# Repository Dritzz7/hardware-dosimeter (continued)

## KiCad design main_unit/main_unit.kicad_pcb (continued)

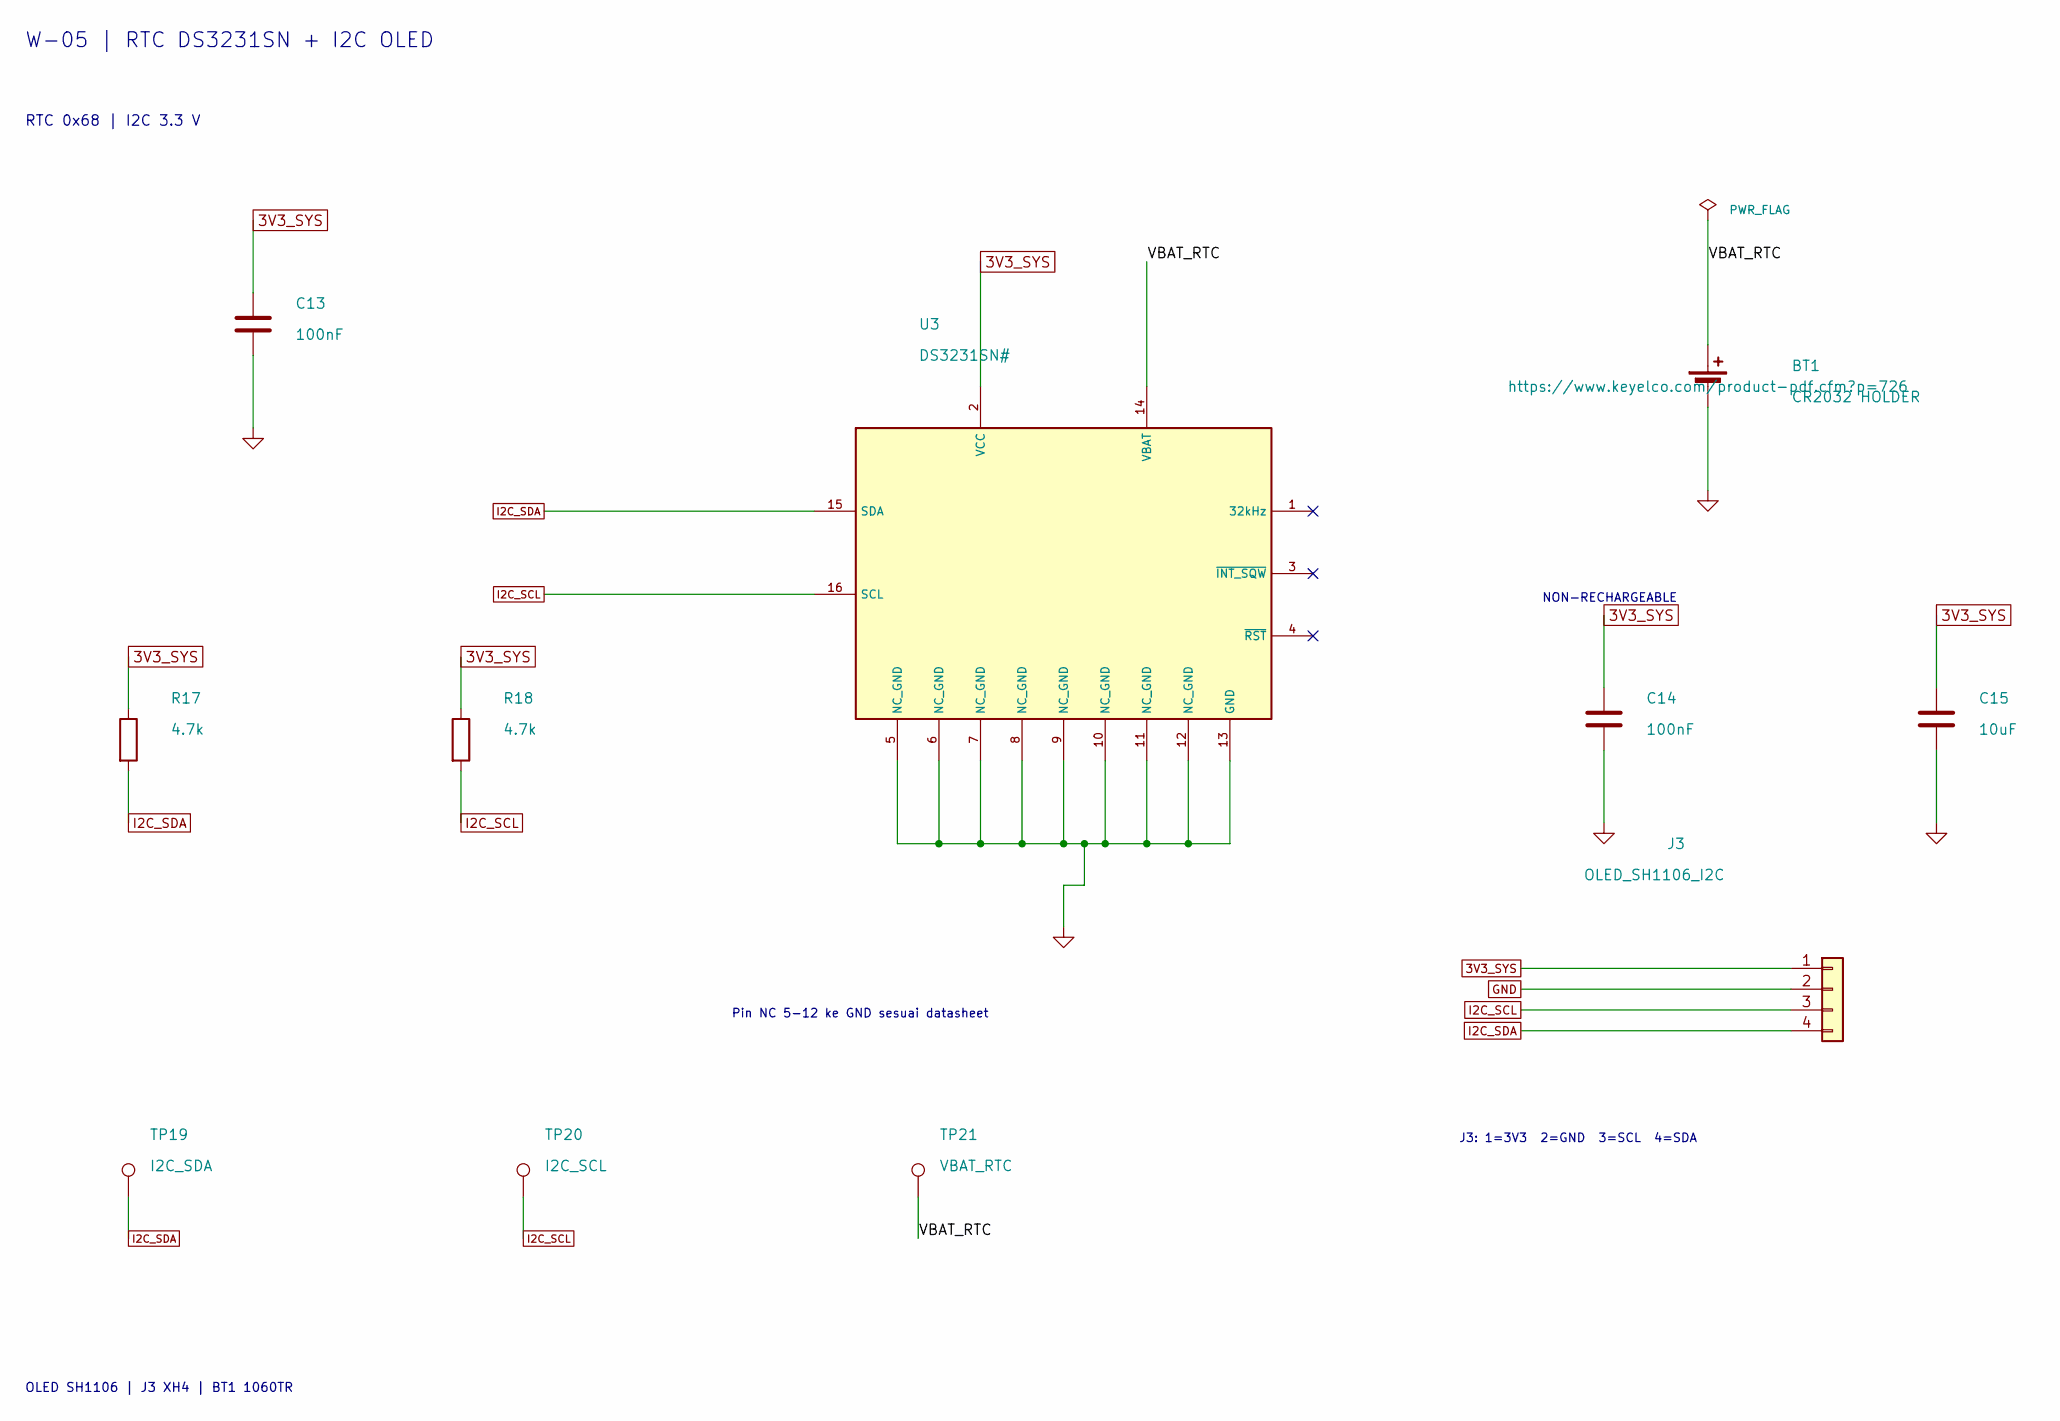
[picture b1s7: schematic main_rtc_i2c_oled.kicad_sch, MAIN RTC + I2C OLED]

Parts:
BT1: CR2032 HOLDER; BatteryHolder_Keystone_1060TR_1x2032; MPN 1060TR; LCSC Part # C238069
C13, C14: 100nF; C_0805_2012Metric; MPN C0805C104K5RACTU; LCSC Part # C3018562
C15: 10uF; C_0805_2012Metric; MPN CL21A106KAYNNNE; LCSC Part # C15850
J3: OLED_SH1106_I2C; JST_XH_B4B-XH-A_1x04_P2.50mm_Vertical; MPN B4B-XH-A(LF)(SN); LCSC Part # C144395
R17, R18: 4.7k; R_0805_2012Metric; MPN RC0805FR-074K7L; LCSC Part # C60816
TP19: I2C_SDA; TestPoint_Pad_D1.5mm; MPN N/A - PCB copper feature
TP20: I2C_SCL; TestPoint_Pad_D1.5mm; MPN N/A - PCB copper feature
TP21: VBAT_RTC; TestPoint_Pad_D1.5mm; MPN N/A - PCB copper feature
U3: DS3231SN#; SOIC-16W_7.5x10.3mm_P1.27mm; MPN DS3231SN#; LCSC Part # C5369307

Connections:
3V3_SYS: C13.1, C14.1, C15.1, J3.1, R17.1, R18.1, U3.2 (VCC); also elsewhere on the board
/MAIN_RTC_I2C_OLED/VBAT_RTC: BT1.1 (+), TP21.1 (1_1), U3.14 (VBAT)
GND: BT1.2 (-), C13.2, C14.2, C15.2, J3.2, U3.5 (NC_GND), U3.6 (NC_GND), U3.7 (NC_GND), U3.8 (NC_GND), U3.9 (NC_GND), U3.10 (NC_GND), U3.11 (NC_GND), U3.12 (NC_GND), U3.13 (GND); also elsewhere on the board
I2C_SCL: J3.3, R18.2, TP20.1 (1_1), U3.16 (SCL); also elsewhere on the board
I2C_SDA: J3.4, R17.2, TP19.1 (1_1), U3.15 (SDA); also elsewhere on the board

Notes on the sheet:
W-05 | RTC DS3231SN + I2C OLED
NON-RECHARGEABLE
J3: 1=3V3 2=GND 3=SCL 4=SDA
Pin NC 5-12 ke GND sesuai datasheet
OLED SH1106 | J3 XH4 | BT1 1060TR
RTC 0x68 | I2C 3.3 V

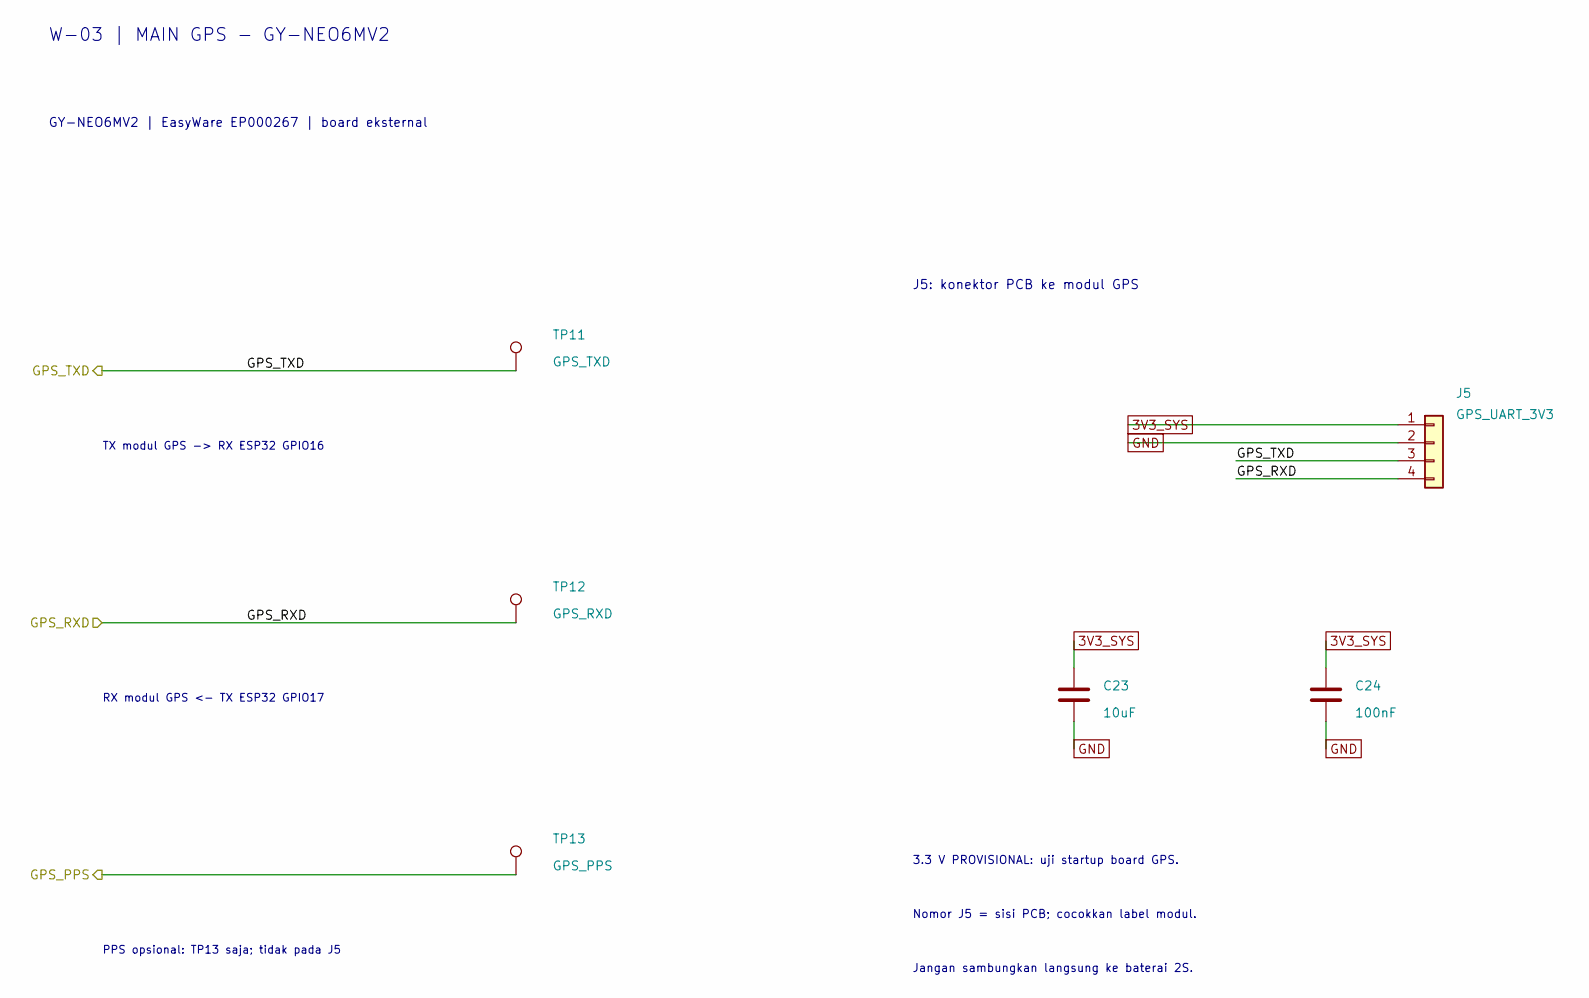
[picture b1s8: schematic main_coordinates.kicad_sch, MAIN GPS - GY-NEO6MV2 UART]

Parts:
C23: 10uF; C_0805_2012Metric; Voltage_Rating >=6.3V; MPN CL21A106KAYNNNE; LCSC Part # C15850
C24: 100nF; C_0805_2012Metric; Voltage_Rating >=6.3V; MPN C0805C104K5RACTU; LCSC Part # C3018562
J5: GPS_UART_3V3; JST_XH_B4B-XH-A_1x04_P2.50mm_Vertical; MPN B4B-XH-A(LF)(SN); LCSC Part # C144395
TP11: GPS_TXD; TestPoint_Pad_D1.5mm; MPN N/A - PCB copper feature
TP12: GPS_RXD; TestPoint_Pad_D1.5mm; MPN N/A - PCB copper feature
TP13: GPS_PPS; TestPoint_Pad_D1.5mm; MPN N/A - PCB copper feature

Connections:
3V3_SYS: C23.1, C24.1, J5.1; also elsewhere on the board
/MAIN_ESP32_PROGRAMMING/GPS_PPS: TP13.1 (1_1); also elsewhere on the board
/MAIN_ESP32_PROGRAMMING/GPS_RXD: J5.4, TP12.1 (1_1); also elsewhere on the board
/MAIN_ESP32_PROGRAMMING/GPS_TXD: J5.3, TP11.1 (1_1); also elsewhere on the board
GND: C23.2, C24.2, J5.2; also elsewhere on the board

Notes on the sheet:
GY-NEO6MV2 | EasyWare EP000267 | board eksternal
J5: konektor PCB ke modul GPS
RX modul GPS <- TX ESP32 GPIO17
PPS opsional: TP13 saja; tidak pada J5
W-03 | MAIN GPS - GY-NEO6MV2
TX modul GPS -> RX ESP32 GPIO16
3.3 V PROVISIONAL: uji startup board GPS.
Nomor J5 = sisi PCB; cocokkan label modul.
Jangan sambungkan langsung ke baterai 2S.

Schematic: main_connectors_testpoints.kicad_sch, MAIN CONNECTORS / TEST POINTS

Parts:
J1: PROG_UART_3V3; PinHeader_1x06_P2.54mm_ZHOURI_1.02mm; MPN 2.54-1*6; LCSC Part # C5156615
TP1: MAIN_EN; TestPoint_Pad_D1.5mm; MPN N/A - PCB copper feature
TP2: MAIN_GPIO0; TestPoint_Pad_D1.5mm; MPN N/A - PCB copper feature
TP3: UART_TX0; TestPoint_Pad_D1.5mm; MPN N/A - PCB copper feature
TP4: UART_RX0; TestPoint_Pad_D1.5mm; MPN N/A - PCB copper feature

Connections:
3V3_SYS: J1.2; also elsewhere on the board
GND: J1.1; also elsewhere on the board
MAIN_EN: J1.5, TP1.1 (1_1); also elsewhere on the board
MAIN_GPIO0: J1.6, TP2.1 (1_1); also elsewhere on the board
UART_RX0: J1.4, TP4.1 (1_1); also elsewhere on the board
UART_TX0: J1.3, TP3.1 (1_1); also elsewhere on the board

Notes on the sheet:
W-08 | MAIN CONNECTORS / TEST POINTS
1 GND | 2 3V3 reference
J4 / TP24-28: MAIN_POWER
RESET/BOOT di MCU | UART 3.3 V | J1 header 2.54 mm
SERVICE UART / PROGRAMMING
3 TX ESP -> RX adapter
TP5-10: MAIN_ADXL345
J1.2: reference only; jangan hubungkan output daya adapter
J1 - KONTRAK PIN PCB
J3 / TP19-21: MAIN_RTC_I2C_OLED
J2 / TP14-18: MAIN_MICROSD
4 RX ESP <- TX adapter
TP22-23: MAIN_HMI
J5 / TP11-13: MAIN_GPS
INDEKS - TETAP DI SHEET FUNGSINYA
5 EN | 6 GPIO0 / BOOT

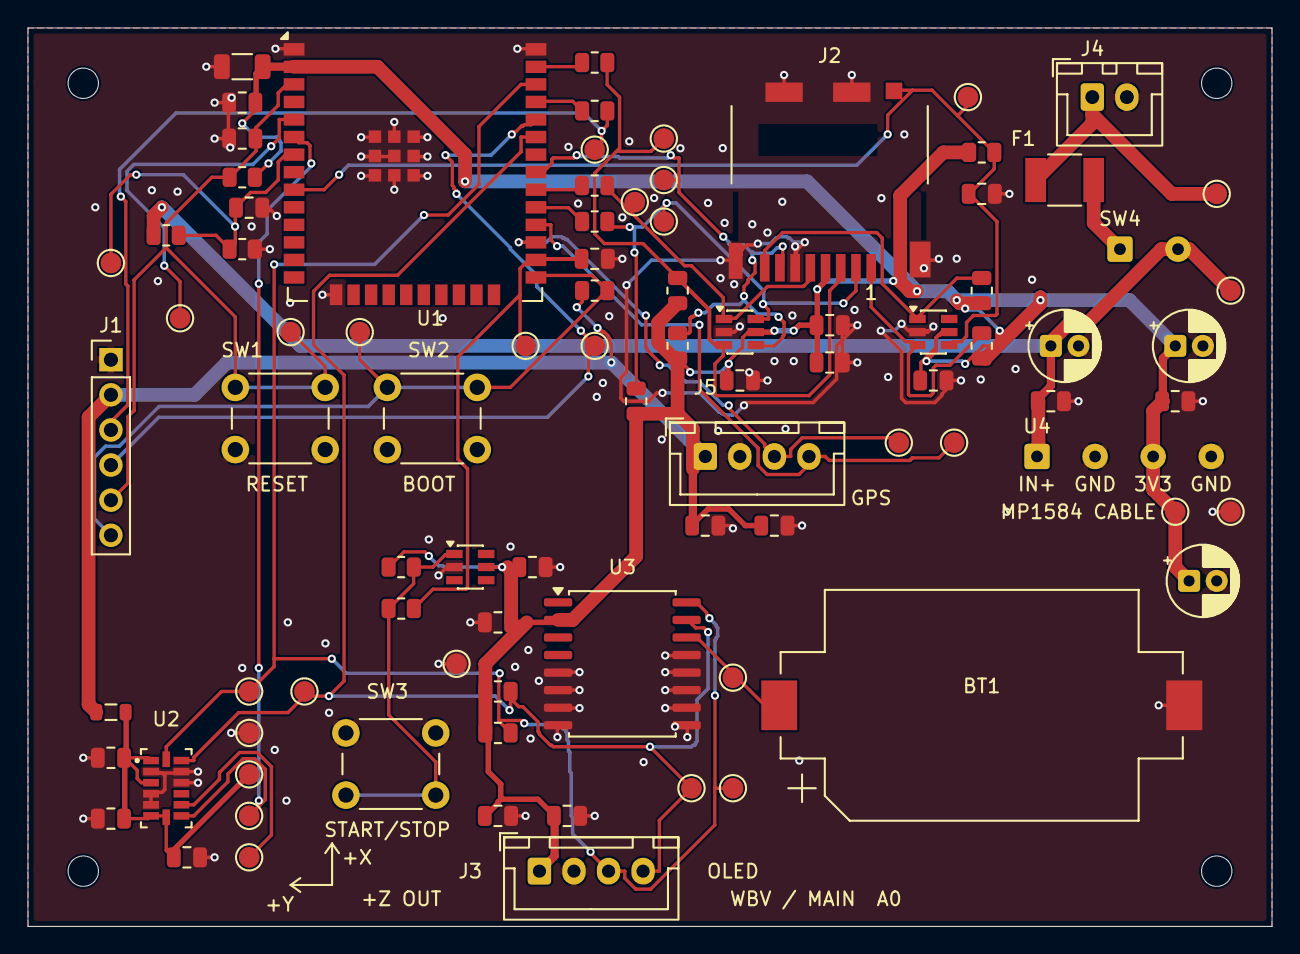
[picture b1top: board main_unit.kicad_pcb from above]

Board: 2 copper layers, 90.0 x 65.0 mm, 93 parts (0 on the bottom side), 32 nets.

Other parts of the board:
H1, H2, H3, H4: M2 mounting PROVISIONAL; MountingHole_2.2mm_M2

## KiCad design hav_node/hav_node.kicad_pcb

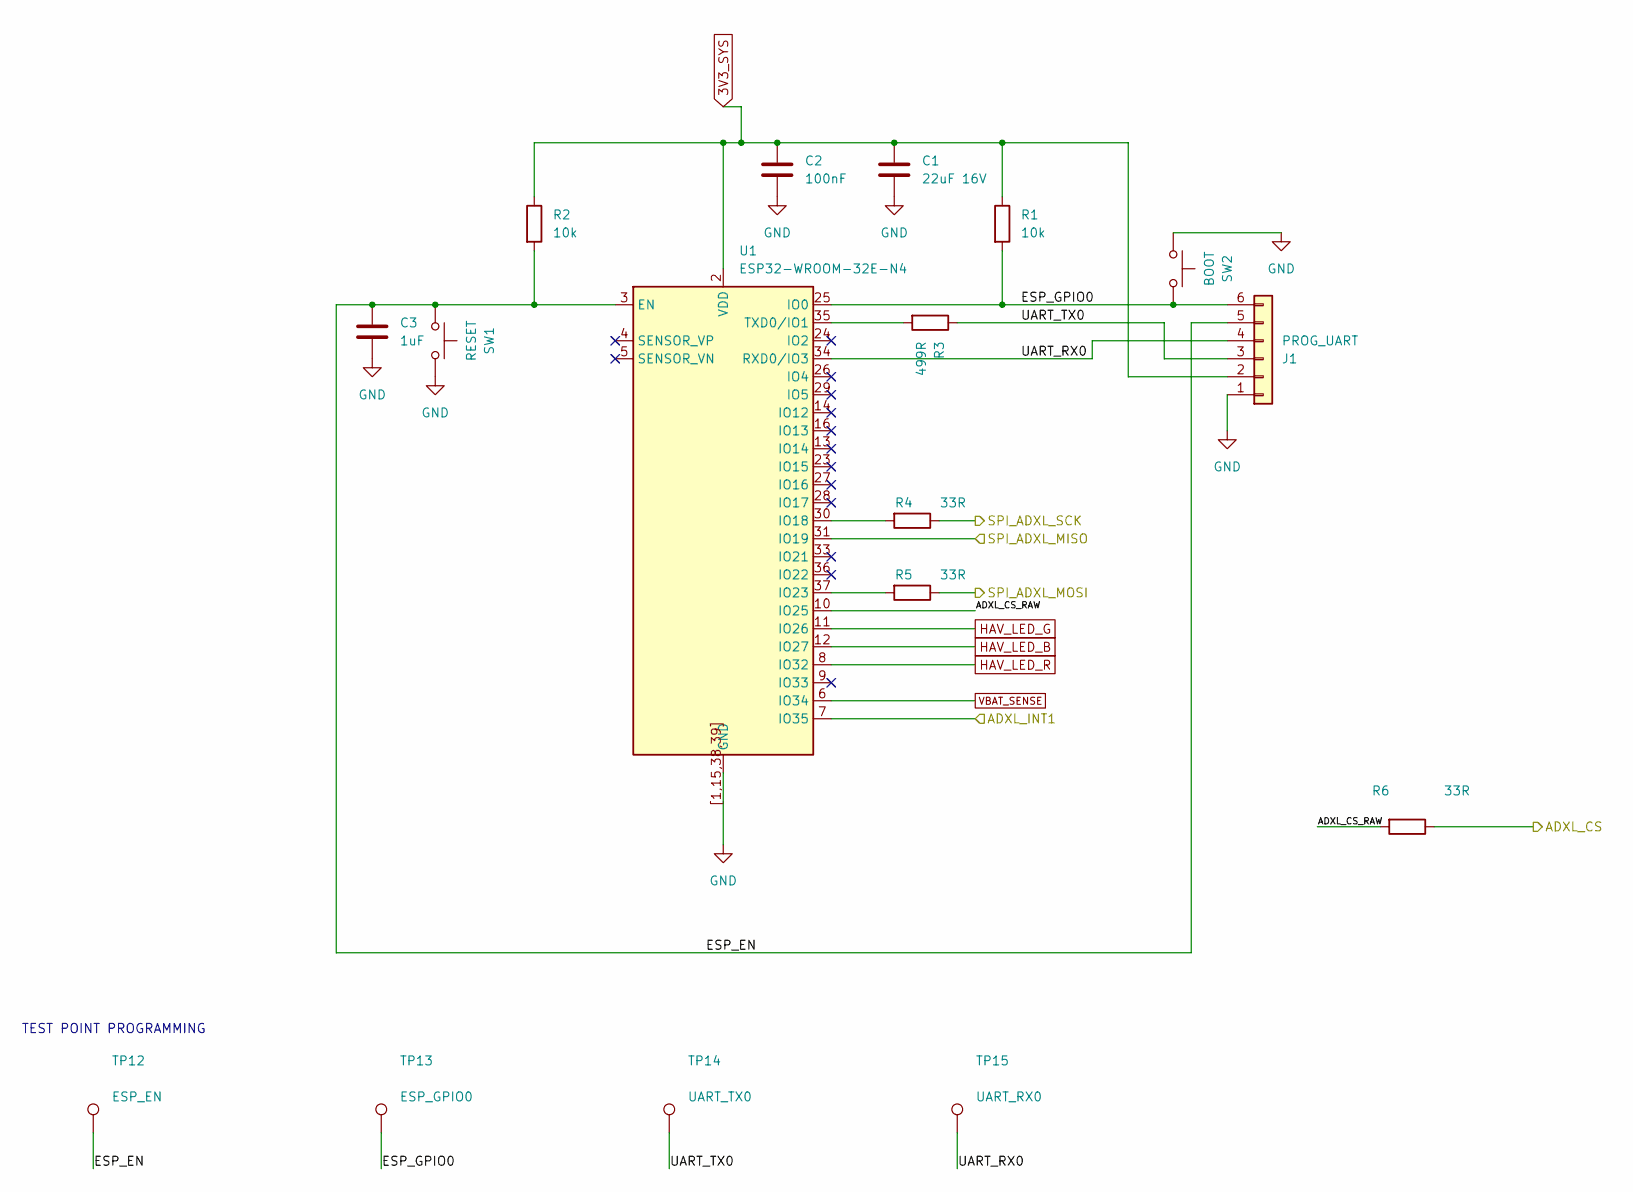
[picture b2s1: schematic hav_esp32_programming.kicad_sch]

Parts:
C1: 22uF 16V; C_1206_3216Metric; MPN CL31A226KOHNNNE; LCSC Part # C90146
C2: 100nF; C_0805_2012Metric; MPN C0805C104K5RACTU; LCSC Part # C3018562
C3: 1uF; C_0805_2012Metric; MPN C0805C105K4RACTU; LCSC Part # C2167376
J1: PROG_UART; PinHeader_1x06_P2.54mm_ZHOURI_1.02mm; MPN 2.54-1*6; LCSC Part # C5156615
R1, R2: 10k; R_0805_2012Metric; MPN RC0805FR-0710KL; LCSC Part # C84376
R3: 499R; R_0805_2012Metric; MPN RC0805FR-07499RL; LCSC Part # C130458
R4, R5, R6: 33R; R_0805_2012Metric; MPN RC0805FR-0733RL; LCSC Part # C126353
SW1: RESET; SW_PUSH_6mm_H4.3mm; MPN B3F-1000; LCSC Part # C93157
SW2: BOOT; SW_PUSH_6mm_H4.3mm; MPN B3F-1000; LCSC Part # C93157
TP12: ESP_EN; TestPoint_Pad_D1.5mm; MPN N/A - bare PCB pad
TP13: ESP_GPIO0; TestPoint_Pad_D1.5mm; MPN N/A - bare PCB pad
TP14: UART_TX0; TestPoint_Pad_D1.5mm; MPN N/A - bare PCB pad
TP15: UART_RX0; TestPoint_Pad_D1.5mm; MPN N/A - bare PCB pad
U1: ESP32-WROOM-32E-N4; ESP32-WROOM-32E_JLC_NoVia; MPN ESP32-WROOM-32E-N4; LCSC Part # C701341

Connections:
3V3_SYS: C1.1, C2.1, J1.2, R1.1, R2.1, U1.2 (VDD); also elsewhere on the board
/ADXL_CS: R6.1; also elsewhere on the board
/ADXL_INT1: U1.7 (IO35); also elsewhere on the board
/HAV_ESP32_PROGRAMMING/ADXL_CS_RAW: R6.2, U1.10 (IO25)
/HAV_ESP32_PROGRAMMING/ESP_EN: C3.1, J1.5, R2.2, SW1.1, TP12.1 (1_1), U1.3 (EN)
/HAV_ESP32_PROGRAMMING/ESP_GPIO0: J1.6, R1.2, SW2.2, TP13.1 (1_1), U1.25 (IO0)
/HAV_ESP32_PROGRAMMING/UART_RX0: J1.4, TP15.1 (1_1), U1.34 (RXD0/IO3)
/HAV_ESP32_PROGRAMMING/UART_TX0: J1.3, R3.1, TP14.1 (1_1)
/SPI_ADXL_MISO: U1.31 (IO19); also elsewhere on the board
/SPI_ADXL_MOSI: R5.1; also elsewhere on the board
/SPI_ADXL_SCK: R4.1; also elsewhere on the board
GND: C1.2, C2.2, C3.2, J1.1, SW1.2, SW2.1, U1.1 (GND), U1.15 (GND), U1.38 (GND), U1.39 (GND), U1.[1,15,38,39] (GND); also elsewhere on the board
HAV_LED_B: U1.12 (IO27); also elsewhere on the board
HAV_LED_G: U1.11 (IO26); also elsewhere on the board
HAV_LED_R: U1.8 (IO32); also elsewhere on the board
unnamed: R4.2, U1.30 (IO18)
unnamed: R5.2, U1.37 (IO23)
unnamed: R3.2, U1.35 (TXD0/IO1)
VBAT_SENSE: U1.6 (IO34); also elsewhere on the board

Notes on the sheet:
TEST POINT PROGRAMMING

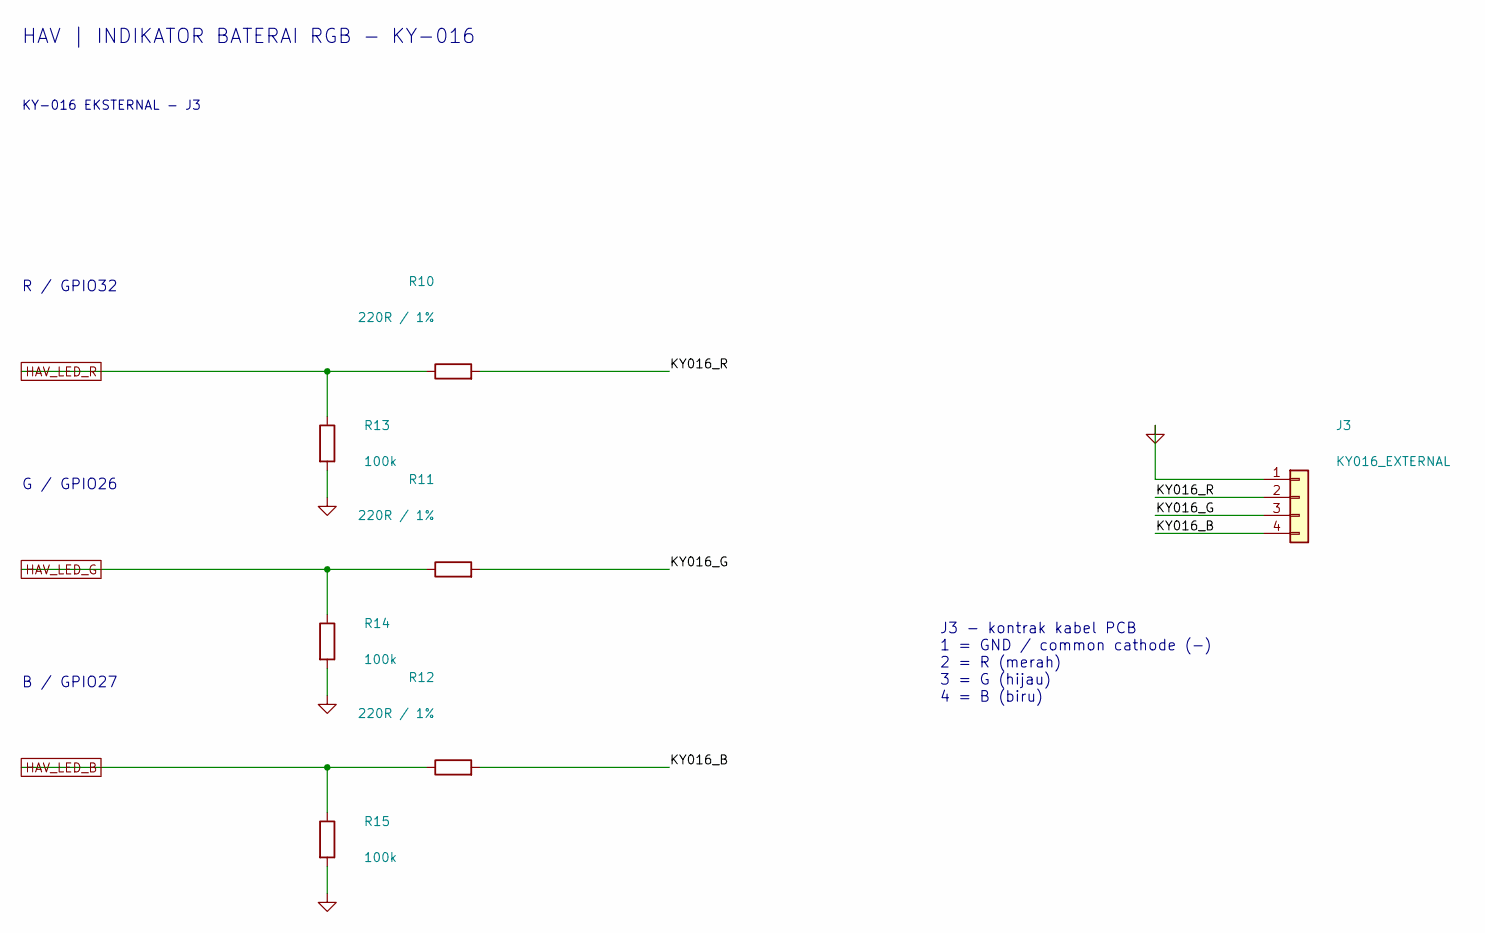
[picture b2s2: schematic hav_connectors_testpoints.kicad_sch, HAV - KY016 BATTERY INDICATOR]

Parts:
J3: KY016_EXTERNAL; JST_XH_B4B-XH-A_1x04_P2.50mm_Vertical; MPN B4B-XH-A(LF)(SN); LCSC Part # C144395
R10, R11, R12: 220R / 1%; R_0805_2012Metric; MPN RC0805FR-07220RL; LCSC Part # C114519
R13, R14, R15: 100k; R_0805_2012Metric; MPN RC0805FR-07100KL; LCSC Part # C96346

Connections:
/HAV_CONNECTORS_TESTPOINTS/KY016_B: J3.4, R12.2
/HAV_CONNECTORS_TESTPOINTS/KY016_G: J3.3, R11.2
/HAV_CONNECTORS_TESTPOINTS/KY016_R: J3.2, R10.2
GND: J3.1, R13.2, R14.2, R15.2; also elsewhere on the board
HAV_LED_B: R12.1, R15.1; also elsewhere on the board
HAV_LED_G: R11.1, R14.1; also elsewhere on the board
HAV_LED_R: R10.1, R13.1; also elsewhere on the board

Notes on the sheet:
KY-016 EKSTERNAL - J3
G / GPIO26
J3 - kontrak kabel PCB 1 = GND / common cathode (-) 2 = R (merah) 3 = G (hijau) 4 = B (biru)
HAV | INDIKATOR BATERAI RGB - KY-016
B / GPIO27
R / GPIO32

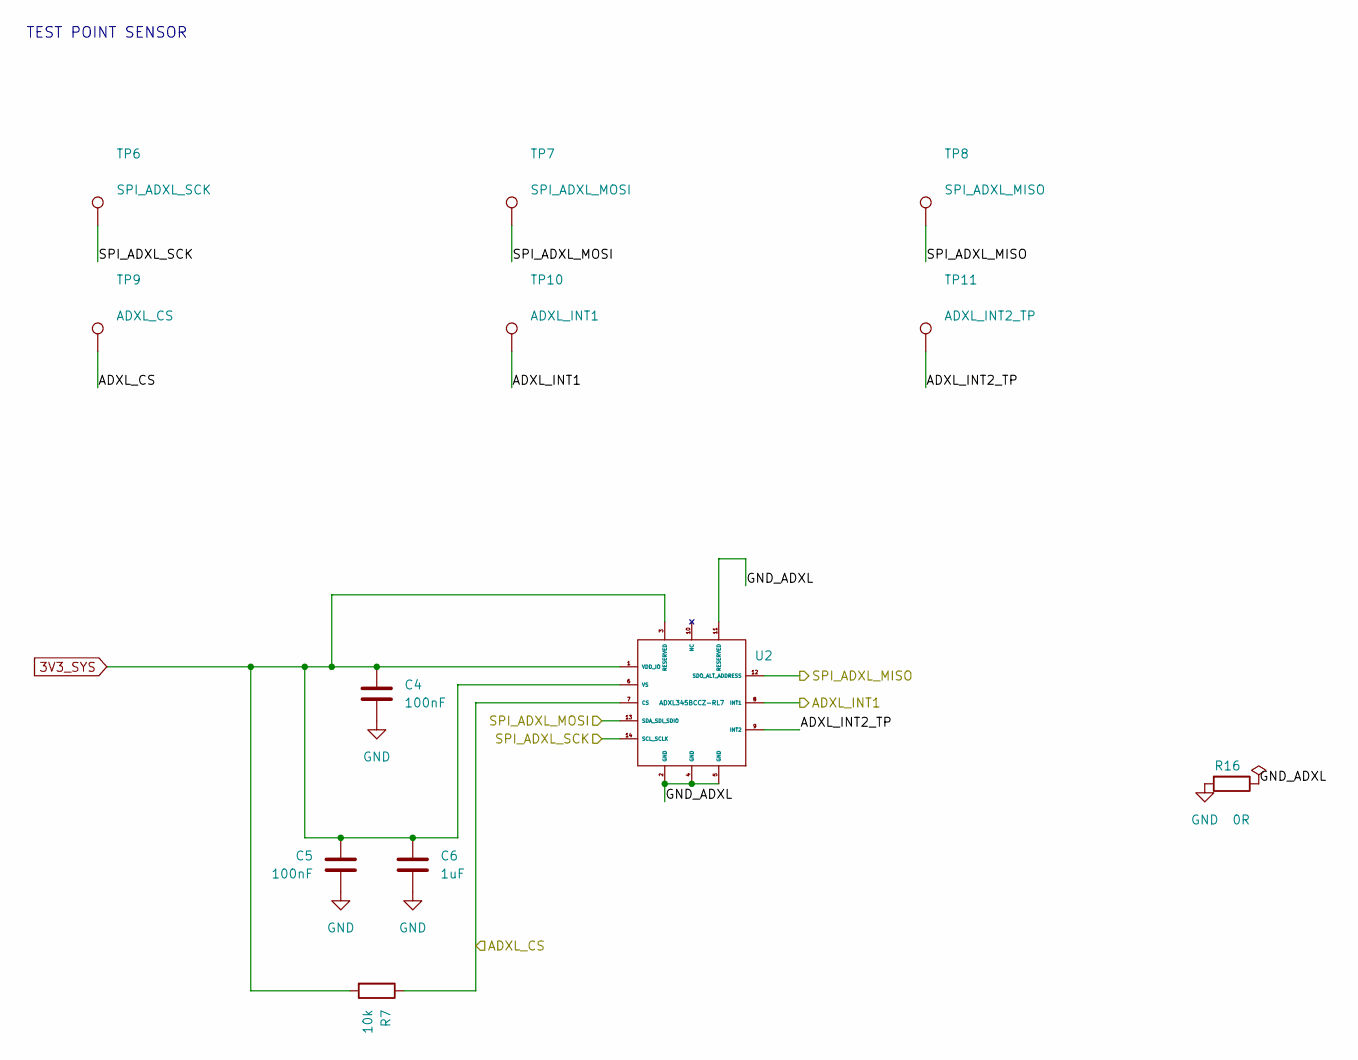
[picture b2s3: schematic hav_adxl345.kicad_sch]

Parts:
C4, C5: 100nF; C_0805_2012Metric; MPN C0805C104K5RACTU; LCSC Part # C3018562
C6: 1uF; C_0805_2012Metric; MPN C0805C105K4RACTU; LCSC Part # C2167376
R7: 10k; R_0805_2012Metric; MPN RC0805FR-0710KL; LCSC Part # C84376
R16: 0R; R_0805_2012Metric; MPN RC0805JR-070RL; LCSC Part # C96345
TP6: SPI_ADXL_SCK; TestPoint_Pad_D1.5mm; MPN N/A - bare PCB pad
TP7: SPI_ADXL_MOSI; TestPoint_Pad_D1.5mm; MPN N/A - bare PCB pad
TP8: SPI_ADXL_MISO; TestPoint_Pad_D1.5mm; MPN N/A - bare PCB pad
TP9: ADXL_CS; TestPoint_Pad_D1.5mm; MPN N/A - bare PCB pad
TP10: ADXL_INT1; TestPoint_Pad_D1.5mm; MPN N/A - bare PCB pad
TP11: ADXL_INT2_TP; TestPoint_Pad_D1.5mm; MPN N/A - bare PCB pad
U2: ADXL345BCCZ-RL7; ADXL345_CC-14-1_ADI_JLC; MPN ADXL345BCCZ-RL7; LCSC Part # C9667

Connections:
3V3_SYS: C4.1, C5.1, C6.1, R7.2, U2.1 (VDD_IO), U2.3 (RESERVED), U2.6 (VS); also elsewhere on the board
/ADXL_CS: R7.1, TP9.1 (1_1), U2.7 (CS); also elsewhere on the board
/ADXL_INT1: TP10.1 (1_1), U2.8 (INT1); also elsewhere on the board
/HAV_ADXL345/ADXL_INT2_TP: TP11.1 (1_1), U2.9 (INT2)
/HAV_ADXL345/GND_ADXL: R16.1, U2.2 (GND), U2.4 (GND), U2.5 (GND), U2.11 (RESERVED)
/SPI_ADXL_MISO: TP8.1 (1_1), U2.12 (SDO_ALT_ADDRESS); also elsewhere on the board
/SPI_ADXL_MOSI: TP7.1 (1_1), U2.13 (SDA_SDI_SDIO); also elsewhere on the board
/SPI_ADXL_SCK: TP6.1 (1_1), U2.14 (SCL_SCLK); also elsewhere on the board
GND: C4.2, C5.2, C6.2, R16.2; also elsewhere on the board

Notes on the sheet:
TEST POINT SENSOR

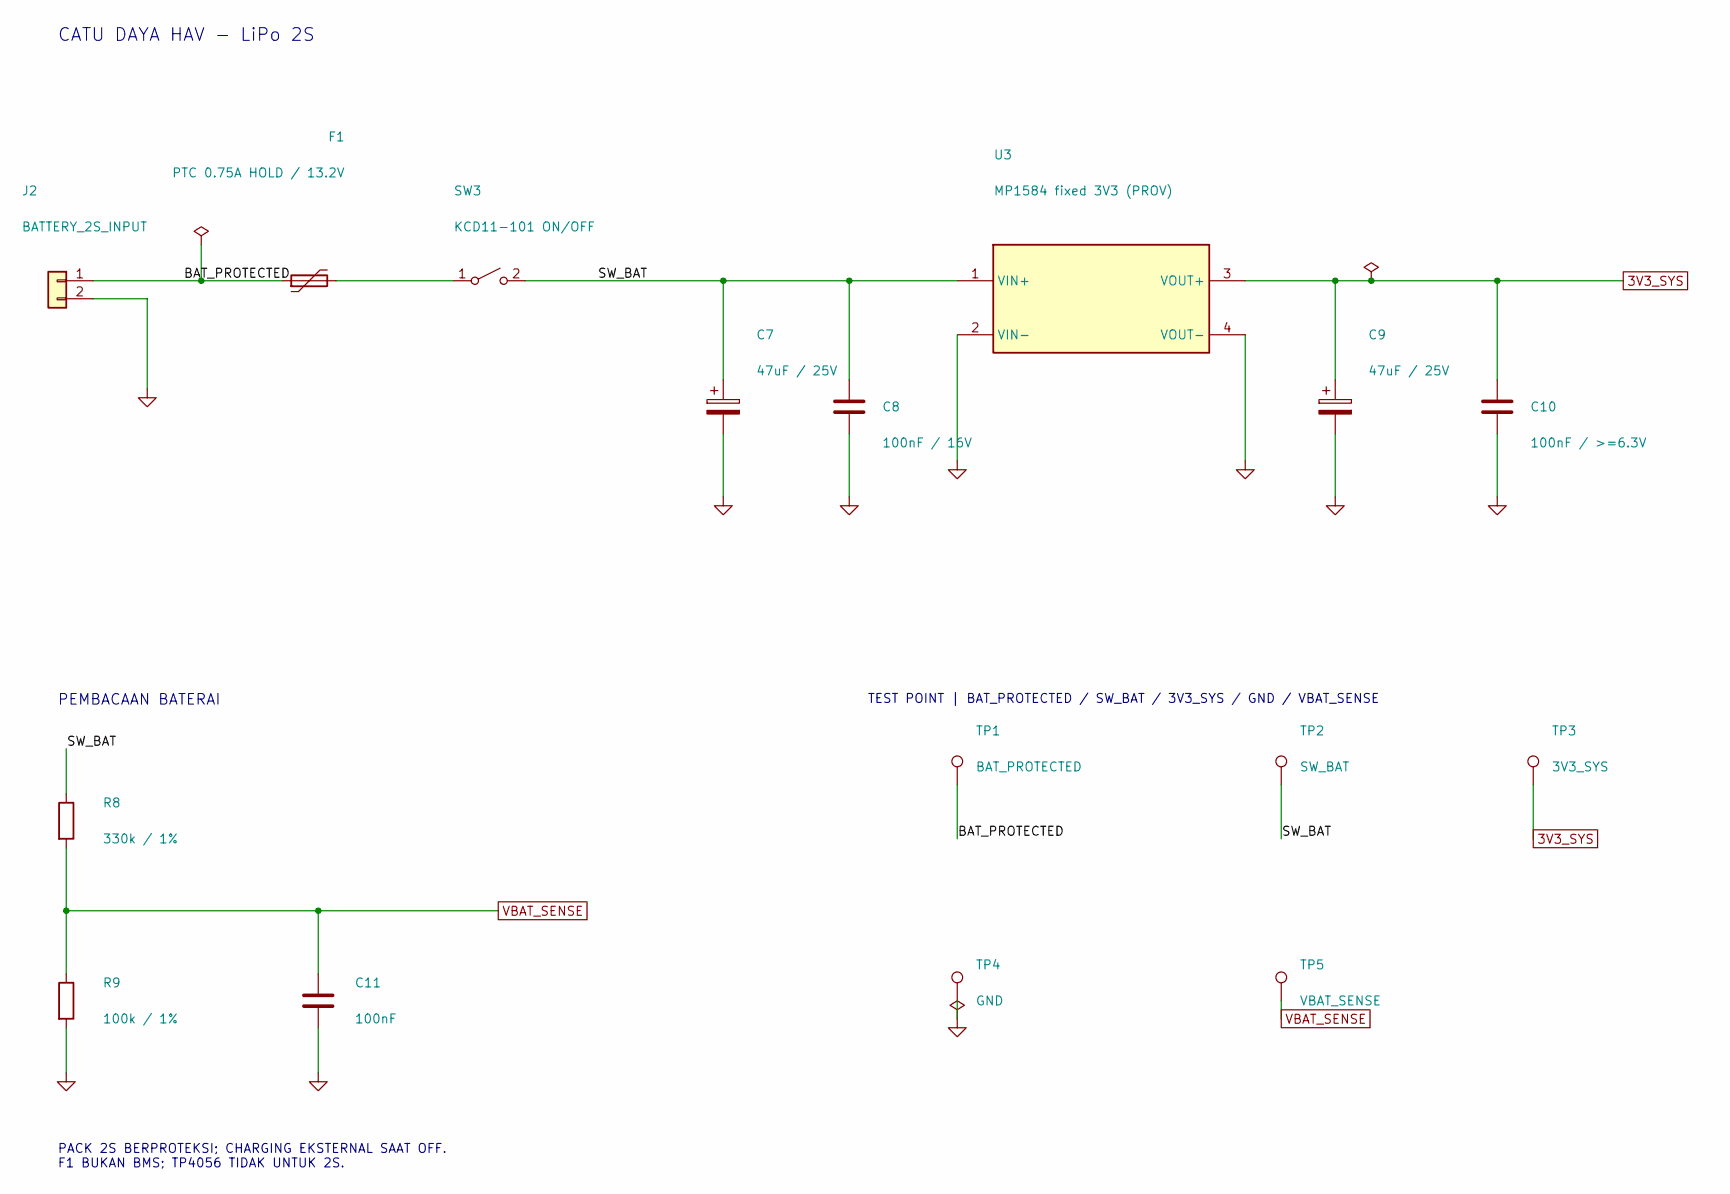
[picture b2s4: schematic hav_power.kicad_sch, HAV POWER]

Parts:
C7, C9: 47uF / 25V; CP_Radial_D5.0mm_P2.00mm_H11mm_Panasonic_FR; MPN EEUFR1E470; LCSC Part # C407893
C8: 100nF / 16V; C_0805_2012Metric; MPN C0805C104K5RACTU; LCSC Part # C3018562
C10: 100nF / >=6.3V; C_0805_2012Metric; MPN C0805C104K5RACTU; LCSC Part # C3018562
C11: 100nF; C_0805_2012Metric; MPN C0805C104K5RACTU; LCSC Part # C3018562
F1: PTC 0.75A HOLD / 13.2V; Fuse_Bourns_MF-MSMF075_1812_Style1; MPN MF-MSMF075-2; LCSC Part # C84140
J2: BATTERY_2S_INPUT; JST_XH_B2B-XH-A_1x02_P2.50mm_Vertical; MPN B2B-XH-A(LF)(SN); LCSC Part # C158012
R8: 330k / 1%; R_0805_2012Metric; MPN RC0805FR-07330KL; LCSC Part # C114528
R9: 100k / 1%; R_0805_2012Metric; MPN RC0805FR-07100KL; LCSC Part # C96346
SW3: KCD11-101 ON/OFF; SolderWire-0.25sqmm_1x02_P4.2mm_D0.65mm_OD1.7mm; MPN OPEN - verify purchased part
TP1: BAT_PROTECTED; TestPoint_Pad_D1.5mm; MPN N/A - bare PCB pad
TP2: SW_BAT; TestPoint_Pad_D1.5mm; MPN N/A - bare PCB pad
TP3: 3V3_SYS; TestPoint_Pad_D1.5mm; MPN N/A - bare PCB pad
TP4: GND; TestPoint_Pad_D1.5mm; MPN N/A - bare PCB pad
TP5: VBAT_SENSE; TestPoint_Pad_D1.5mm; MPN N/A - bare PCB pad
U3: MP1584 fixed 3V3 (PROV); SolderWire-0.25sqmm_1x04_P4.2mm_D0.65mm_OD1.7mm; MPN OPEN - verify purchased part

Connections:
3V3_SYS: C9.1, C10.1, TP3.1 (1_1), U3.3 (VOUT+); also elsewhere on the board
/HAV_POWER/BAT_PROTECTED: F1.1, J2.1, TP1.1 (1_1)
/HAV_POWER/SW_BAT: C7.1, C8.1, R8.1, SW3.2 (B), TP2.1 (1_1), U3.1 (VIN+)
GND: C7.2, C8.2, C9.2, C10.2, C11.2, J2.2, R9.2, TP4.1 (1_1), U3.2 (VIN-), U3.4 (VOUT-); also elsewhere on the board
unnamed: F1.2, SW3.1 (A)
VBAT_SENSE: C11.1, R8.2, R9.1, TP5.1 (1_1); also elsewhere on the board

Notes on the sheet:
CATU DAYA HAV - LiPo 2S
PEMBACAAN BATERAI
TEST POINT | BAT_PROTECTED / SW_BAT / 3V3_SYS / GND / VBAT_SENSE
PACK 2S BERPROTEKSI; CHARGING EKSTERNAL SAAT OFF. F1 BUKAN BMS; TP4056 TIDAK UNTUK 2S.

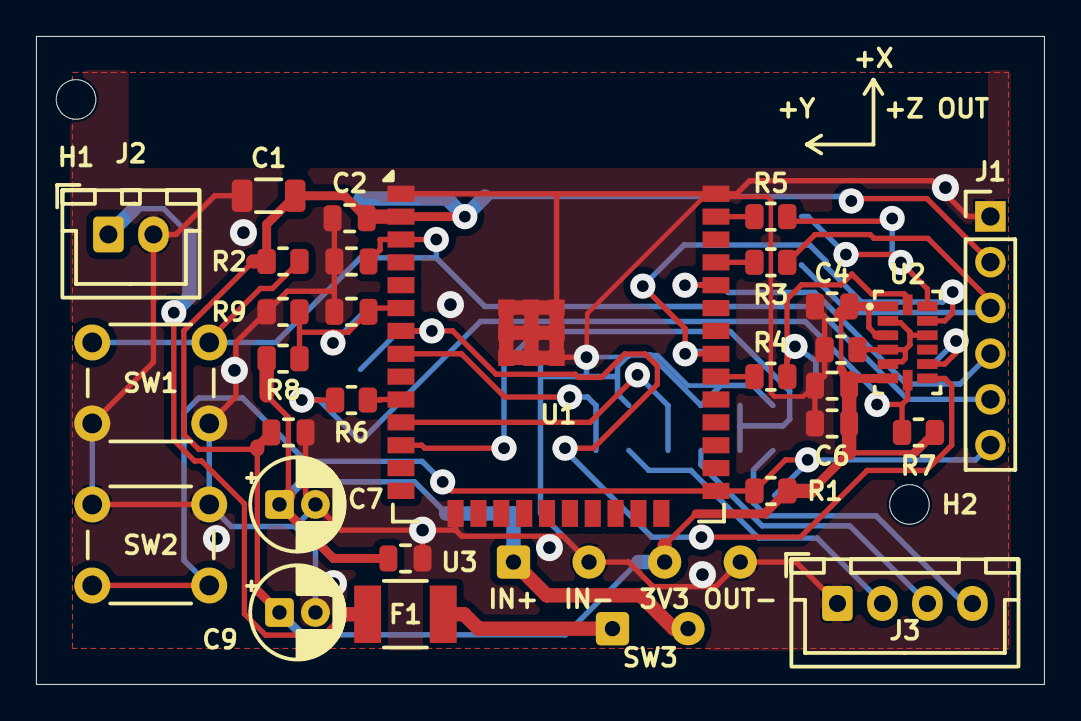
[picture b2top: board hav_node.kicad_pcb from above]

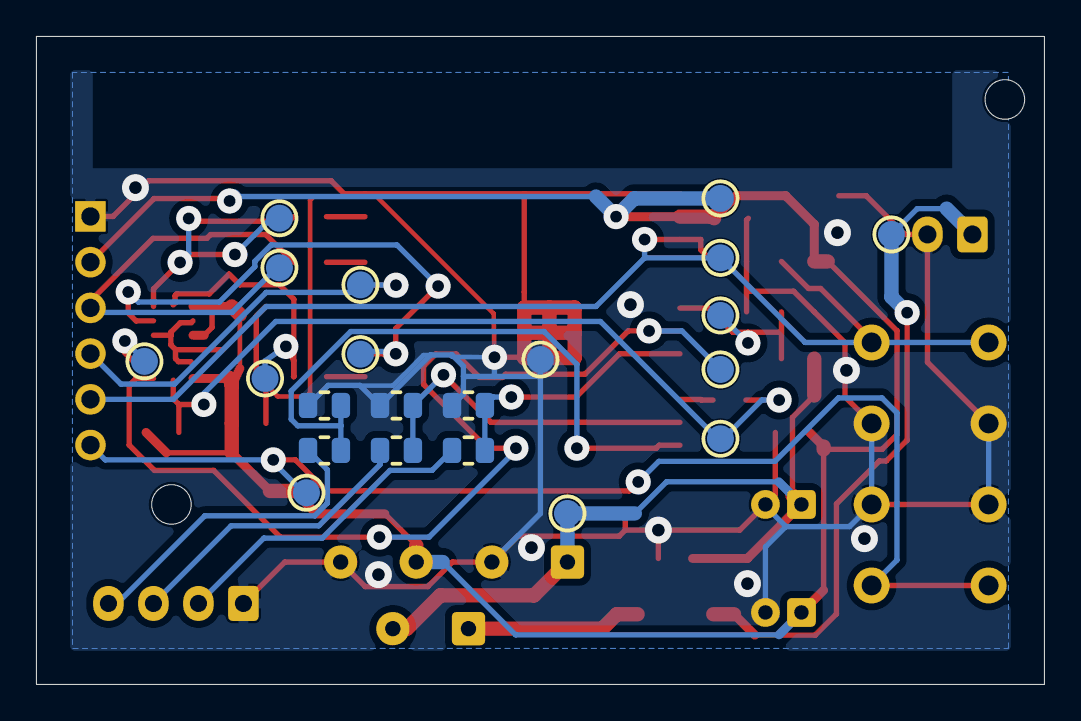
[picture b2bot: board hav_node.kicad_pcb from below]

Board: 2 copper layers, 56.0 x 36.0 mm, 54 parts (21 on the bottom side), 27 nets.

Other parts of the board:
H1, H2: M2 mounting; MountingHole_2.2mm_M2_BothSides

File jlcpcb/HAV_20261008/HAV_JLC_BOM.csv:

"Comment","Designator","Footprint","LCSC Part #"
"22 uF; 16 V; X5R; 10%; 1206; CL31A226KOHNNNE","C1","C_1206_3216Metric","C90146"
"100 nF; 50 V; X7R; 10%; 0805; C0805C104K5RACTU","C2,C4,C5,C8,C10,C11","C_0805_2012Metric","C3018562"
"1 uF; 16 V; X7R; 10%; 0805; C0805C105K4RACTU","C3,C6","C_0805_2012Metric","C2167376"
"47 uF; 25 V; 20%; polar; radial D5 x H11 mm; pitch 2 mm; EEUFR1E470","C7,C9","CP_Radial_D5.0mm_P2.00mm_H11mm_Panasonic_FR","C407893"
"PTC; hold 0.75 A; trip 1.5 A; max 13.2 V; 1812 Style 1; MF-MSMF075-2","F1","Fuse_Bourns_MF-MSMF075_1812_Style1","C84140"
"Male THT straight 1x6; pitch 2.54 mm; insulator 2.54 mm; pin 0.63 mm square; 2.54-1*6","J1","PinHeader_1x06_P2.54mm_ZHOURI_1.02mm","C5156615"
"XH vertical 2 pin; pitch 2.50 mm; 3 A; B2B-XH-A(LF)(SN)","J2","JST_XH_B2B-XH-A_1x02_P2.50mm_Vertical","C158012"
"XH vertical 4 pin; pitch 2.50 mm; 3 A; B4B-XH-A(LF)(SN)","J3","JST_XH_B4B-XH-A_1x04_P2.50mm_Vertical","C144395"
"10 kohm; 1%; 0.125 W; 0805; RC0805FR-0710KL","R1,R2,R7","R_0805_2012Metric","C84376"
"499 ohm; 1%; 0.125 W; 0805; RC0805FR-07499RL","R3","R_0805_2012Metric","C130458"
"33 ohm; 1%; 0.125 W; 0805; RC0805FR-0733RL","R4,R5,R6","R_0805_2012Metric","C126353"
"330 kohm; 1%; 0.125 W; 0805; RC0805FR-07330KL","R8","R_0805_2012Metric","C114528"
"100 kohm; 1%; 0.125 W; 0805; RC0805FR-07100KL","R9,R13,R14,R15","R_0805_2012Metric","C96346"
"220 ohm; 1%; 0.125 W; 0805; RC0805FR-07220RL","R10,R11,R12","R_0805_2012Metric","C114519"
"0 ohm jumper; 0805; WAJIB terpasang, bukan DNP; RC0805JR-070RL","R16","R_0805_2012Metric","C96345"
"Momentary SPST-NO; 6x6 mm; H4.3 mm; RESET / BOOT; B3F-1000","SW1,SW2","SW_PUSH_6mm_H4.3mm","C93157"
"WROOM-32E; 4 MB flash; PCB antenna; bukan DevKit; ESP32-WROOM-32E-N4","U1","ESP32-WROOM-32E_JLC_NoVia","C701341"
"Bare IC; LGA-14 CC-14-1; 3x5 mm; pitch 0.8 mm; ADXL345BCCZ-RL7","U2","ADXL345_CC-14-1_ADI_JLC","C9667"
